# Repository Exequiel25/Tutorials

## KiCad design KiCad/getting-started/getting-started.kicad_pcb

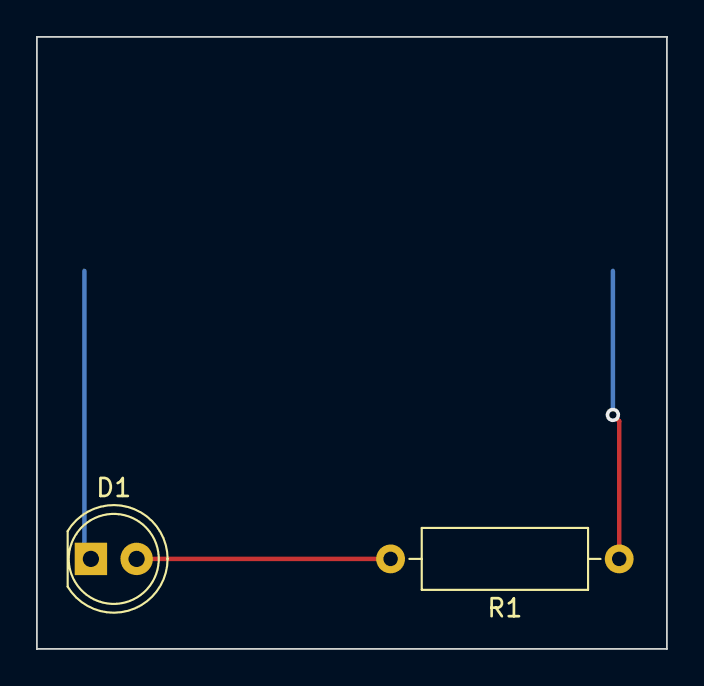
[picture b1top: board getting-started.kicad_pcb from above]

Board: 2 copper layers, 35.0 x 34.0 mm, 3 parts (1 on the bottom side), 2 nets.

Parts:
BT1: 3V; BatteryHolder_Keystone_1058_1x2032
D1: red; LED_D5.0mm
R1: 1k; R_Axial_DIN0309_L9.0mm_D3.2mm_P12.70mm_Horizontal

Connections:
GND: BT1.2 (-), D1.1 (K)
unnamed: D1.2 (A), R1.2

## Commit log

2022-01-19 Python tutorial
2022-01-19 Matplotlib commit
2022-01-22 Octave tutorial
2022-03-11 last
2022-08-31 Videos rotos
2023-03-19 Nuevo tutorial: Introduccion a python junto a Matlab y simulink
2023-03-19 Introducciones a las gráficas con Python
2023-03-23 Markdown
2023-03-23 Python as MATLAB 'lo basico'
2023-04-01 agregado de índices para búsquedas rápidas
2023-04-01 agregado de índices para búsquedas rápidas y Kernerl restart
2023-04-02 Sist 1er Orden (incompleto), solo respuesta al escalón
2023-04-02 updating checkpoints
2023-04-02 Indices y mejor orden
2023-04-02 bkup
2023-04-02 untitled removed
2023-04-02 pequeños arreglos
2023-04-02 mejorando librerías genéricas y reemplazando control.matlab por control
2023-04-02 error en 2.B. corregido
2023-04-02 recopilado funciones genéricas
2023-04-02 comenzando el análisis en 2do orden
2023-04-02 pequeñas correciones
2023-04-04 Actualización de funciones y correción de errores
2023-04-04 Actualización de funciones y respuesta al escalón en todos los sistemas
2023-05-20 stablishing kernel Control
2023-05-25 edit jupyter with VSCode
2023-06-11 kicad tutorial
2023-12-27 backup
2025-04-01 New Repository-Python as MATLAB
